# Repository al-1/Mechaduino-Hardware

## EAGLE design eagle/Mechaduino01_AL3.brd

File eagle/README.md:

here you can find the changes of this branch compared to the original.

I had some play around with the original eagle files. My goals was to changed them to use more part I do have in stock. In the last iteration I was also trying to get all components on one side.
This also is not ready yet. I do not know. I do not know yet whether I ever will order modified board or just use the original.

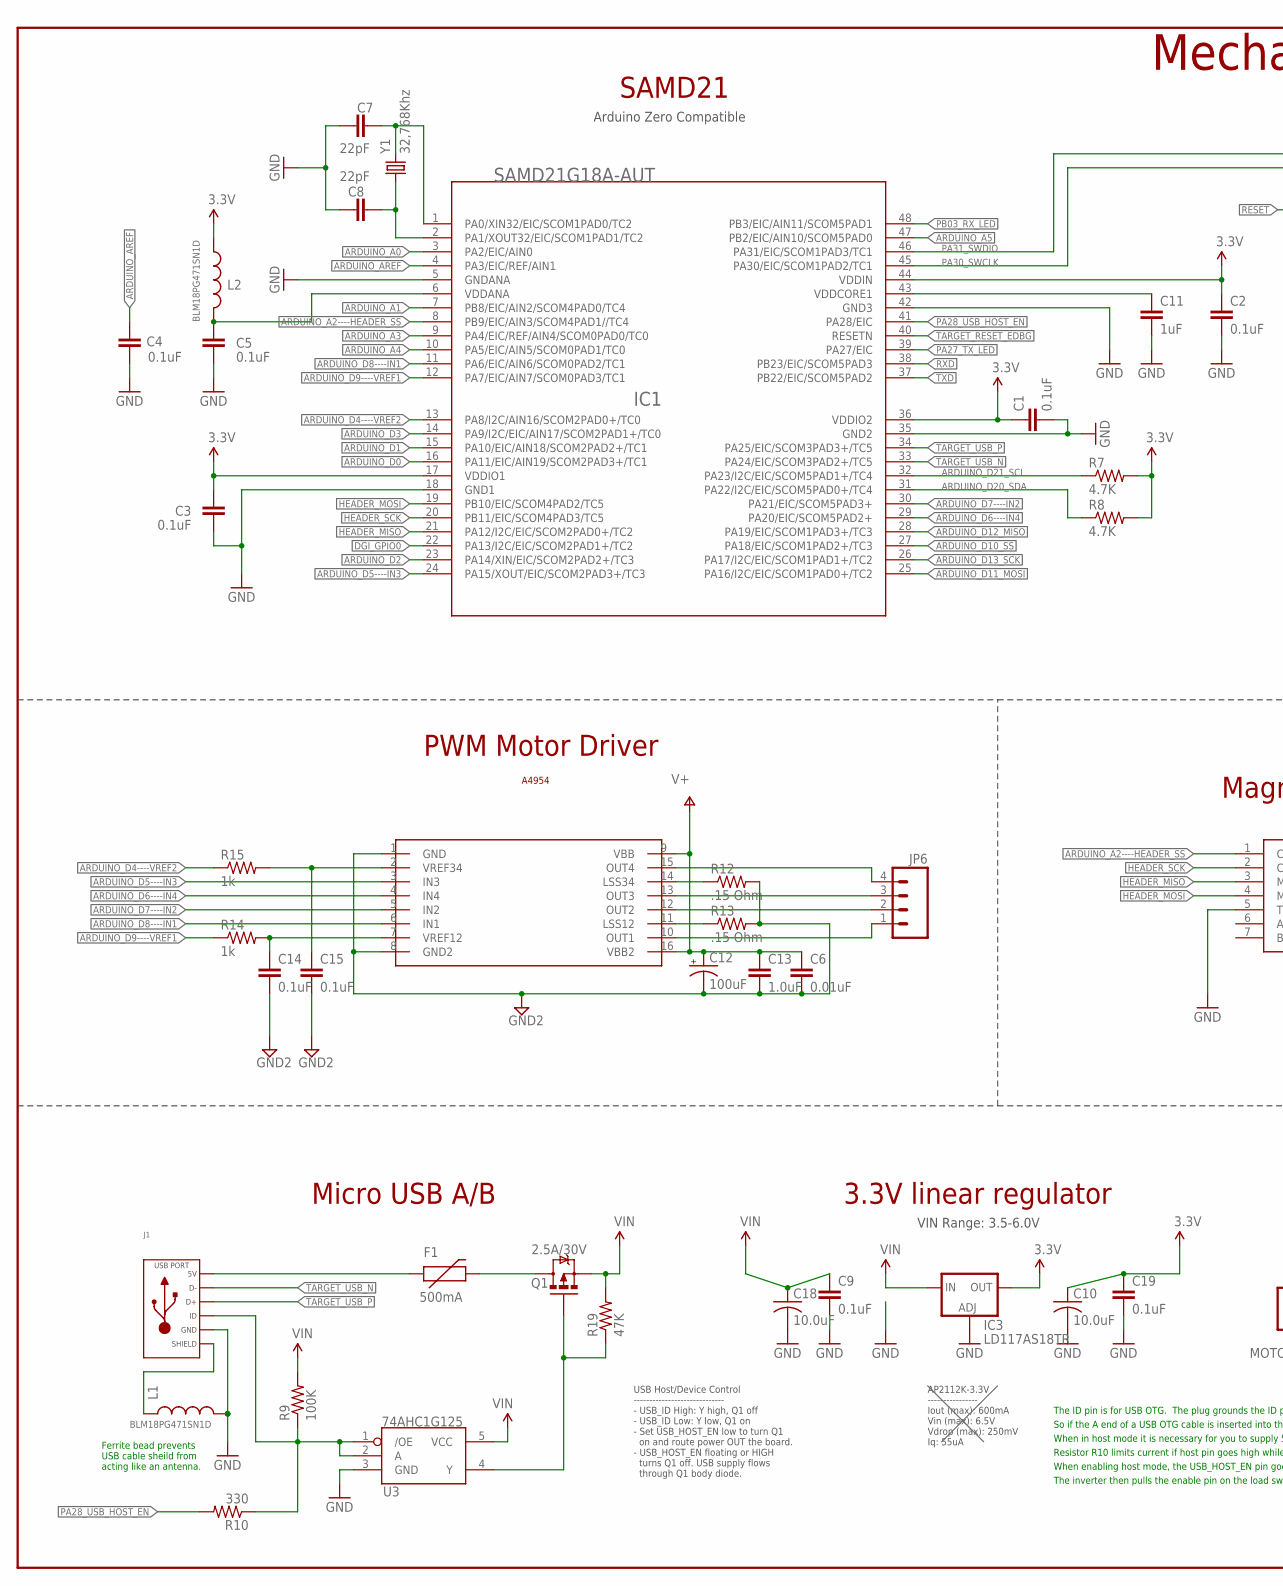
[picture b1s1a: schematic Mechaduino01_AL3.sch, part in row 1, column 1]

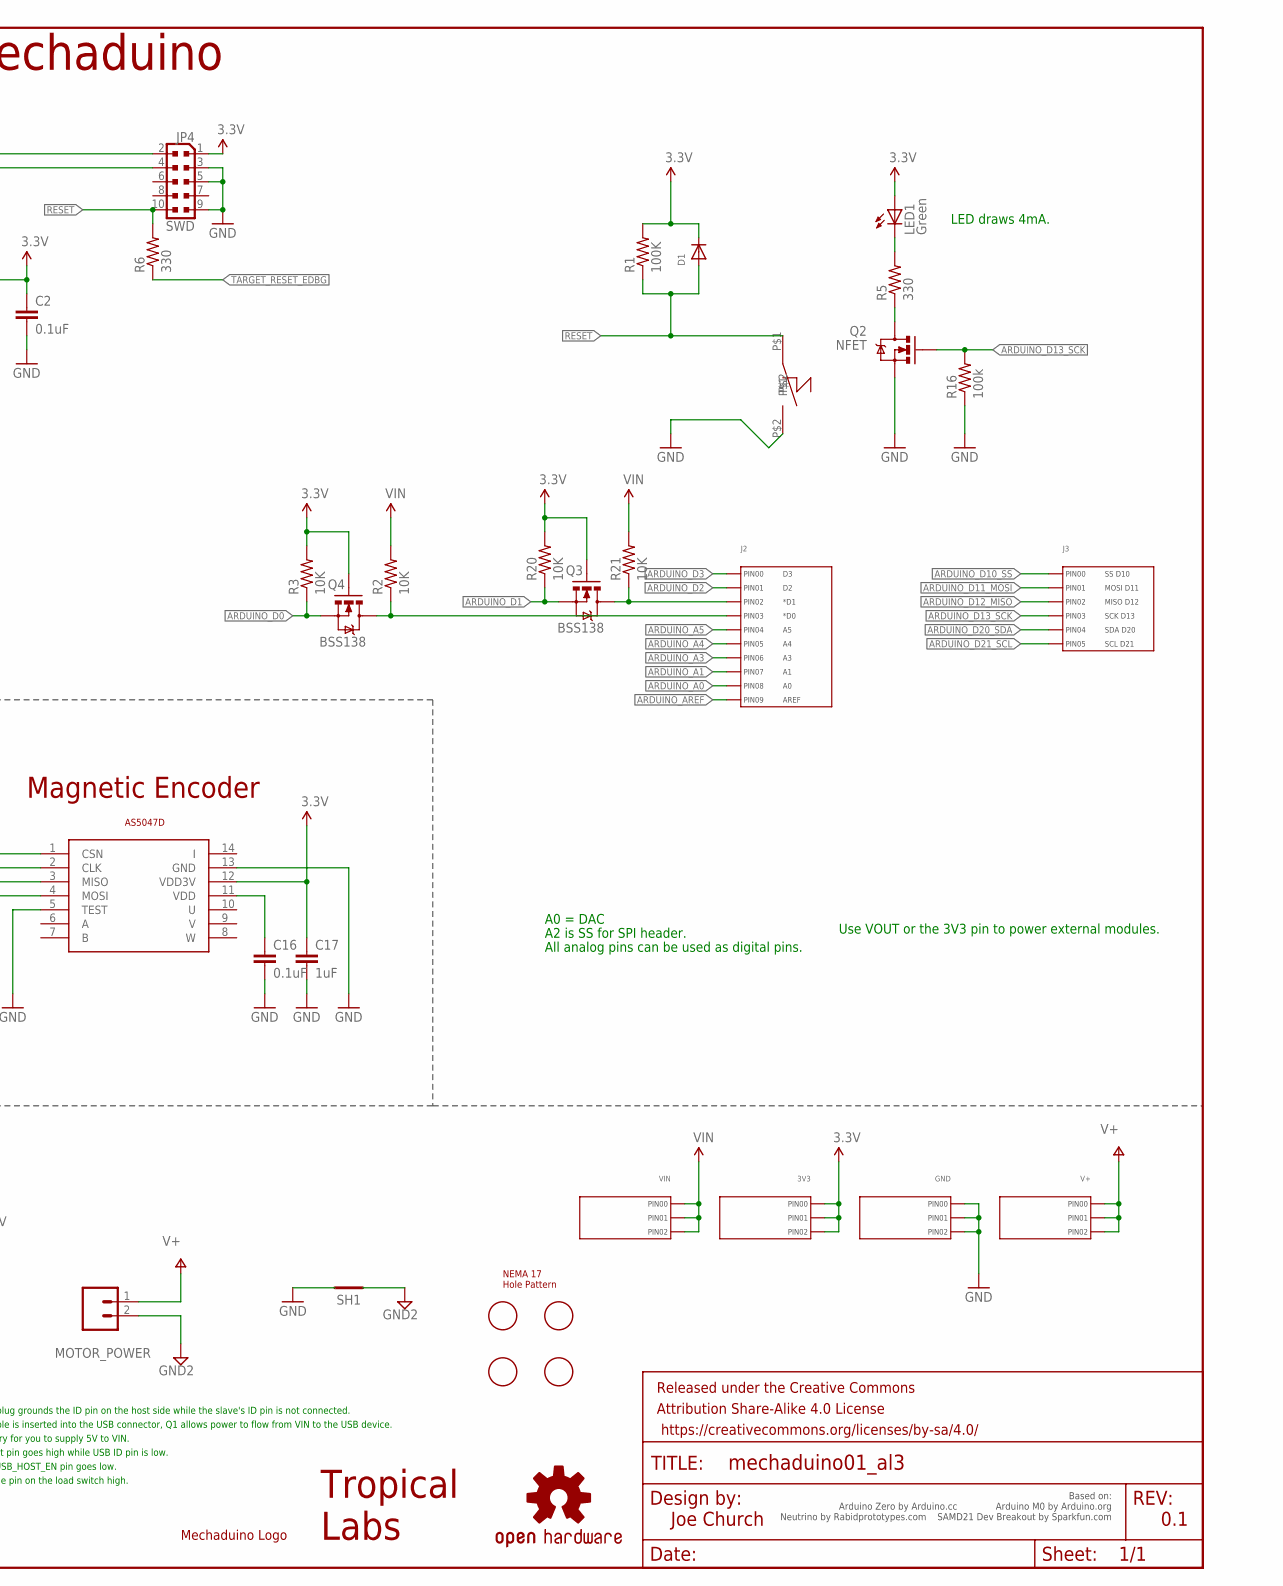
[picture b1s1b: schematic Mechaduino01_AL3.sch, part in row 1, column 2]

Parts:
3V3: HEADER_01X03_PTH_2.54MM; PTH_2.54MM_01X03
C1, C2, C3, C4, C5, C9, C14, C15, C16, C19: 0.1uF; 0402-CAP
C6: 0.01uF; 0402-CAP
C7, C8: 22pF; 0402-CAP
C10, C18: 10.0uF; C0805
C11, C17: 1uF; 0402-CAP
C12: 100uF; PANASONIC_D
C13: 1.0uF; 0603-CAP
D1: DIODESOD-523; SOD-523
F1: 500mA; PTC-1206
FRAME1: FRAME-LEDGER; CREATIVE_COMMONS
GND: HEADER_01X03_PTH_2.54MM; PTH_2.54MM_01X03
IC1: SAMD21G18A-AUT; INTEGRATEDCIRCUITS_TQFP48-7X7
IC3: LD117AS18TR; SOT223
J1: USB_MICRO_RIGHT; MICROUSB-RIGHT
J2: HEADER_01X10_PTH_2.54MM; PTH_2.54MM_01X10
J3: HEADER_01X06_PTH_2.54MM; PTH_2.54MM_01X06
JP4: SWD; CONNETTORI_PINHEAD-2X5-P127
JP6: M04PTH; 1X04
L1, L2: BLM18PG471SN1D; 0603-TDK
LED1: Green; CHIPLED_0805
LOGO4: OSHW-LOGOL-COPPER; OSHW-LOGO-L_COPPER
MOTOR_POWER: M025MM; SCREWTERMINAL-5MM-2
Q1: 2.5A/30V; SOT23-3
Q2: NFET; SOT323
Q3, Q4: BSS138; SOT23-3
R1, R9: 100K; R0402-VISHAY
R2, R3, R20, R21: 10K; R0402-VISHAY
R5, R6, R10: 330; R0402-VISHAY
R7, R8: 4.7K; R0402-VISHAY
R12, R13: .15 Ohm; R1206
R14, R15: 1k; R0402-VISHAY
R16: 100k; R0402-VISHAY
R19: 47K; 0603-RES
S1: SMD_SWITCH; SMDSWITCH
SH1: SHORT-HA5; SHORT_ALL-50
U3: 74AHC1G125; SOT23-5
U$1: AVAGO_DRIVER; TSSOP16
U$2: NEMA17_HOLE_PATTERN
U$3: TROPICAL_LABS_LOGO_1LOGO3; LOGO3
U$4: AS5047D; TSSOP14
U$5: MECHADUINO_LOGO
V+: HEADER_01X03_PTH_2.54MM; PTH_2.54MM_01X03
VIN: HEADER_01X03_PTH_2.54MM; PTH_2.54MM_01X03
Y1: 32,768Khz; CRYSTAL-SMD-2.0X1.2

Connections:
3.3V: 3V3.P$1 (PIN0), 3V3.P$2 (PIN1), 3V3.P$3 (PIN2), C1.1, C2.1, C3.2, C10.1, C17.1, C19.1, D1.K (C), IC1.17 (VDDIO1), IC1.36 (VDDIO2), IC1.44 (VDDIN), IC3.2 (OUT), IC3.4 (OUT), JP4.1, L2.1, LED1.A, Q3.1 (G), Q4.1 (G), R1.2, R3.2, R7.2, R8.2, R20.2, U$4.12 (VDD3V)
ARDUINO_A0: IC1.3 (PA2/EIC/AIN0), J2.P$9 (PIN8)
ARDUINO_A1: IC1.7 (PB8/EIC/AIN2/SCOM4PAD0/TC4), J2.P$8 (PIN7)
ARDUINO_A2----HEADER_SS: IC1.8 (PB9/EIC/AIN3/SCOM4PAD1//TC4), U$4.1 (CSN)
ARDUINO_A3: IC1.9 (PA4/EIC/REF/AIN4/SCOM0PAD0/TC0), J2.P$7 (PIN6)
ARDUINO_A4: IC1.10 (PA5/EIC/AIN5/SCOM0PAD1/TC0), J2.P$6 (PIN5)
ARDUINO_A5: IC1.47 (PB2/EIC/AIN10/SCOM5PAD0), J2.P$5 (PIN4)
ARDUINO_AREF: C4.1, IC1.4 (PA3/EIC/REF/AIN1), J2.P$10 (PIN9)
ARDUINO_D0: IC1.16 (PA11/EIC/AIN19/SCOM2PAD3+/TC1), Q4.2 (S), R3.1
ARDUINO_D1: IC1.15 (PA10/EIC/AIN18/SCOM2PAD2+/TC1), Q3.2 (S), R20.1
ARDUINO_D2: IC1.23 (PA14/XIN/EIC/SCOM2PAD2+/TC3), J2.P$2 (PIN1)
ARDUINO_D3: IC1.14 (PA9/I2C/EIC/AIN17/SCOM2PAD1+/TC0), J2.P$1 (PIN0)
ARDUINO_D4----VREF2: IC1.13 (PA8/I2C/AIN16/SCOM2PAD0+/TC0), R15.1
ARDUINO_D5----IN3: IC1.24 (PA15/XOUT/EIC/SCOM2PAD3+/TC3), U$1.3 (IN3)
ARDUINO_D6----IN4: IC1.29 (PA20/EIC/SCOM5PAD2+), U$1.4 (IN4)
ARDUINO_D7----IN2: IC1.30 (PA21/EIC/SCOM5PAD3+), U$1.5 (IN2)
ARDUINO_D8----IN1: IC1.11 (PA6/EIC/AIN6/SCOM0PAD2/TC1), U$1.6 (IN1)
ARDUINO_D9----VREF1: IC1.12 (PA7/EIC/AIN7/SCOM0PAD3/TC1), R14.1
ARDUINO_D10_SS: IC1.27 (PA18/EIC/SCOM1PAD2+/TC3), J3.P$1 (PIN0)
ARDUINO_D11_MOSI: IC1.25 (PA16/I2C/EIC/SCOM1PAD0+/TC2), J3.P$2 (PIN1)
ARDUINO_D12_MISO: IC1.28 (PA19/EIC/SCOM1PAD3+/TC3), J3.P$3 (PIN2)
ARDUINO_D13_SCK: IC1.26 (PA17/I2C/EIC/SCOM1PAD1+/TC2), J3.P$4 (PIN3), Q2.1 (G), R16.2
ARDUINO_D20_SDA: IC1.31 (PA22/I2C/EIC/SCOM5PAD0+/TC4), J3.P$5 (PIN4), R8.1
ARDUINO_D21_SCL: IC1.32 (PA23/I2C/EIC/SCOM5PAD1+/TC4), J3.P$6 (PIN5), R7.1
DGI_GPIO0: IC1.22 (PA13/I2C/EIC/SCOM2PAD1+/TC2)
GND: C1.2, C2.2, C3.1, C4.2, C5.2, C7.1, C8.1, C9.2, C10.2, C11.2, C16.2, C17.2, C18.2, C19.2, GND.P$1 (PIN0), GND.P$2 (PIN1), GND.P$3 (PIN2), IC1.5 (GNDANA), IC1.18 (GND1), IC1.35 (GND2), IC1.42 (GND3), IC3.1 (ADJ), J1.5 (GND), JP4.3, JP4.5, JP4.9, L1.2, Q2.2 (S), R16.1, S1.P$2, SH1.2, U3.3 (GND), U$4.5 (TEST), U$4.13 (GND)
GND2: C6.2, C12.-, C13.2, C14.2, C15.2, MOTOR_POWER.2, R12.2, R13.2, SH1.1, U$1.1 (GND), U$1.8 (GND2)
HEADER_MISO: IC1.21 (PA12/I2C/EIC/SCOM2PAD0+/TC2), U$4.3 (MISO)
HEADER_MOSI: IC1.19 (PB10/EIC/SCOM4PAD2/TC5), U$4.4 (MOSI)
HEADER_SCK: IC1.20 (PB11/EIC/SCOM4PAD3/TC5), U$4.2 (CLK)
HV1: J2.P$3 (PIN2), Q3.3 (D), R21.1
HV2: J2.P$4 (PIN3), Q4.3 (D), R2.1
unnamed: LED1.C, R5.2
unnamed: R12.1, U$1.14 (LSS34)
unnamed: Q2.3 (D), R5.1
unnamed: R13.1, U$1.11 (LSS12)
unnamed: C15.1, R15.2, U$1.2 (VREF34)
unnamed: J1.4 (ID), R9.1, R10.1, U3.1 (/OE), U3.2 (A)
unnamed: JP6.4, U$1.15 (OUT4)
unnamed: JP6.1, U$1.10 (OUT1)
unnamed: JP6.2, U$1.12 (OUT2)
unnamed: JP6.3, U$1.13 (OUT3)
unnamed: C16.1, U$4.11 (VDD)
unnamed: C14.1, R14.2, U$1.7 (VREF12)
unnamed: F1.2, Q1.3 (D)
unnamed: Q1.1 (G), R19.1, U3.4 (Y)
unnamed: F1.1, J1.1 (5V)
PA00_XIN32: C7.2, IC1.1 (PA0/XIN32/EIC/SCOM1PAD0/TC2), Y1.2
PA01_XOUT32: C8.2, IC1.2 (PA1/XOUT32/EIC/SCOM1PAD1/TC2), Y1.1
PA27_TX_LED: IC1.39 (PA27/EIC)
PA28_USB_HOST_EN: IC1.41 (PA28/EIC), R10.2
PA30_SWCLK: IC1.45 (PA30/EIC/SCOM1PAD2/TC1), JP4.4
PA31_SWDIO: IC1.46 (PA31/EIC/SCOM1PAD3/TC1), JP4.2
PB03_RX_LED: IC1.48 (PB3/EIC/AIN11/SCOM5PAD1)
RESET: D1.A, JP4.10, R1.1, R6.2, S1.P$1
RXD: IC1.38 (PB23/EIC/SCOM5PAD3)
SHIELD: J1.S1 (SLD), J1.S2 (SLD), J1.S3 (SLD), J1.S4 (SLD), J1.S5 (SLD), J1.S6 (SLD), J1.S7 (SLD), J1.S8 (SLD), L1.1
TARGET_RESET_EDBG: IC1.40 (RESETN), R6.1
TARGET_USB_N: IC1.33 (PA24/EIC/SCOM3PAD2+/TC5), J1.2 (D-)
TARGET_USB_P: IC1.34 (PA25/EIC/SCOM3PAD3+/TC5), J1.3 (D+)
TXD: IC1.37 (PB22/EIC/SCOM5PAD2)
V+: C6.1, C12.+, C13.1, MOTOR_POWER.1, U$1.9 (VBB), U$1.16 (VBB2), V+.P$1 (PIN0), V+.P$2 (PIN1), V+.P$3 (PIN2)
VDDANA: C5.1, IC1.6 (VDDANA), L2.2
VDDCORE: C11.1, IC1.43 (VDDCORE1)
VIN: C9.1, C18.1, IC3.3 (IN), Q1.2 (S), R2.2, R9.2, R19.2, R21.2, U3.5 (VCC), VIN.P$1 (PIN0), VIN.P$2 (PIN1), VIN.P$3 (PIN2)

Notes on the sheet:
A0 = DAC
All analog pins can be used as digital pins.
LED draws 4mA.
A2 is SS for SPI header.
Use VOUT or the 3V3 pin to power external modules.
Ferrite bead prevents USB cable sheild from acting like an antenna.
The ID pin is for USB OTG. The plug grounds the ID pin on the host side while the slave's ID pin is not connected.
So if the A end of a USB OTG cable is inserted into the USB connector, Q1 allows power to flow from VIN to the USB device.
3.3V linear regulator
When in host mode it is necessary for you to supply 5V to VIN.
When enabling host mode, the USB_HOST_EN pin goes low.
Resistor R10 limits current if host pin goes high while USB ID pin is low.
The inverter then pulls the enable pin on the load switch high.
Magnetic Encoder
SAMD21
PWM Motor Driver
VIN Range: 3.5-6.0V
AP2112K-3.3V ---------------- Iout (max): 600mA Vin (max): 6.5V Vdrop (max): 250mV Iq: 55uA
USB Host/Device Control ----------------------------- - USB_ID High: Y high, Q1 off - USB_ID Low: Y low, Q1 on - Set USB_HOST_EN low to turn Q1 on and route power OUT the board. - USB_HOST_EN floating or HIGH turns Q1 off. USB supply flows through Q1 body diode.
A4954
Micro USB A/B
Joe Church
Based on: Arduino Zero by Arduino.cc Arduino M0 by Arduino.org Neutrino by Rabidprototypes.com SAMD21 Dev Breakout by Sparkfun.com
0.1
Arduino Zero Compatible
Mechaduino

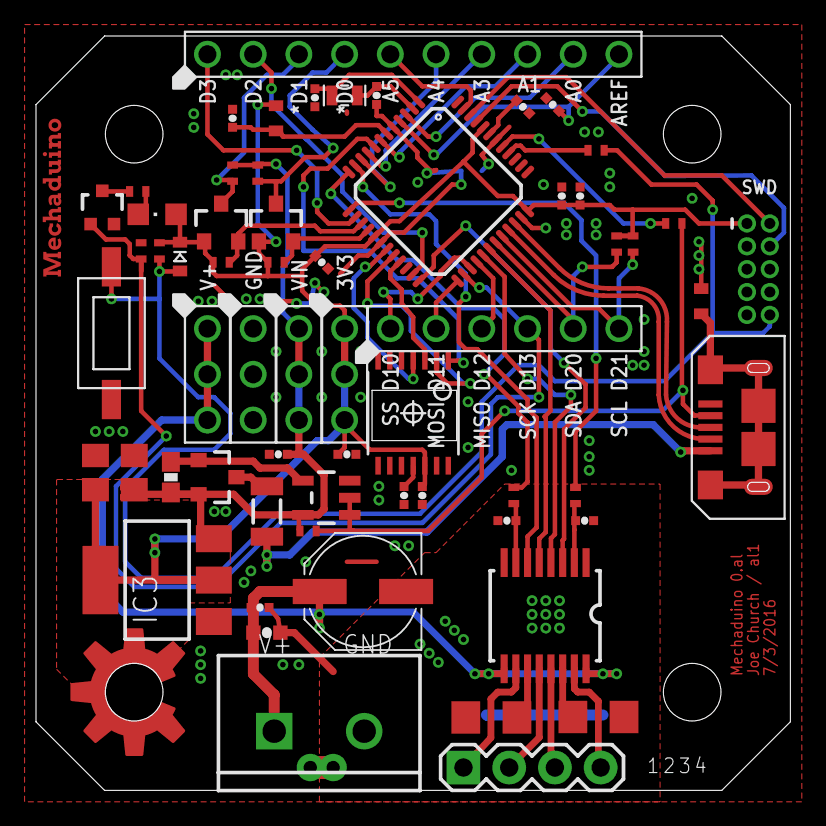
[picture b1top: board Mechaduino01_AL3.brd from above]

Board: 2 copper layers, 41.9 x 41.9 mm, 68 parts (0 on the bottom side), 60 nets.

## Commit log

2016-07-09 some ideas of me (al1) to the board layout
2016-07-09 added readme in /eagle and cleanup
2016-07-09 .../eagle readme correction

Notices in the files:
parts and their libraries:
SparkFun-Connectors: Licensing: Creative Commons ShareAlike 4.0 International - https://creativecommons.org/licenses/by-sa/4.0
SparkFun-Aesthetics: Released under the Creative Commons Attribution Share-Alike 4.0 License
SparkFun-Aesthetics: https://creativecommons.org/licenses/by-sa/4.0
